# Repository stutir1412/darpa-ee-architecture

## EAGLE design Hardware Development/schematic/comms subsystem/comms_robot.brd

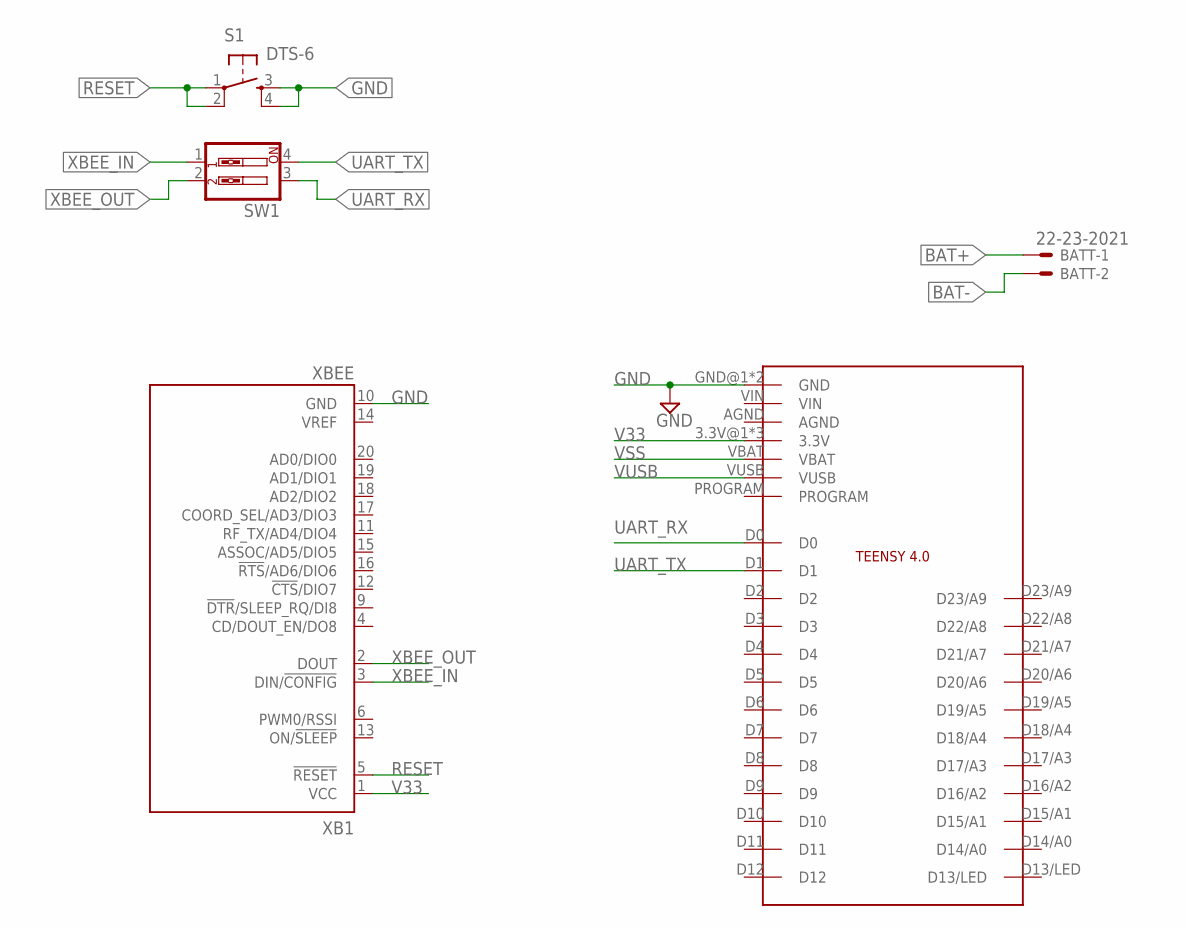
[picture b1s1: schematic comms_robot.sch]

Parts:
BATT: 22-23-2021
S1: DTS-6
SW1: SW_DIP-2; EDG-02
U$1: TEENSY4.0
XB1: XBEE

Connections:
BAT+: BATT.1
BAT-: BATT.2
GND: S1.3, S1.4, U$1.GND@1 (GND), U$1.GND@2 (GND), XB1.10 (GND)
RESET: S1.1, S1.2, XB1.5 (!RESET)
UART_RX: SW1.3, U$1.D0
UART_TX: SW1.4, U$1.D1
V33: U$1.3.3V@1 (3.3V), U$1.3.3V@2 (3.3V), U$1.ON/OFF (3.3V), XB1.1 (VCC)
VSS: U$1.VBAT
VUSB: U$1.VUSB
XBEE_IN: SW1.1, XB1.3 (DIN/!CONFIG)
XBEE_OUT: SW1.2, XB1.2 (DOUT)

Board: 2 copper layers, 5 parts (0 on the bottom side), 7 nets, no tracks yet.

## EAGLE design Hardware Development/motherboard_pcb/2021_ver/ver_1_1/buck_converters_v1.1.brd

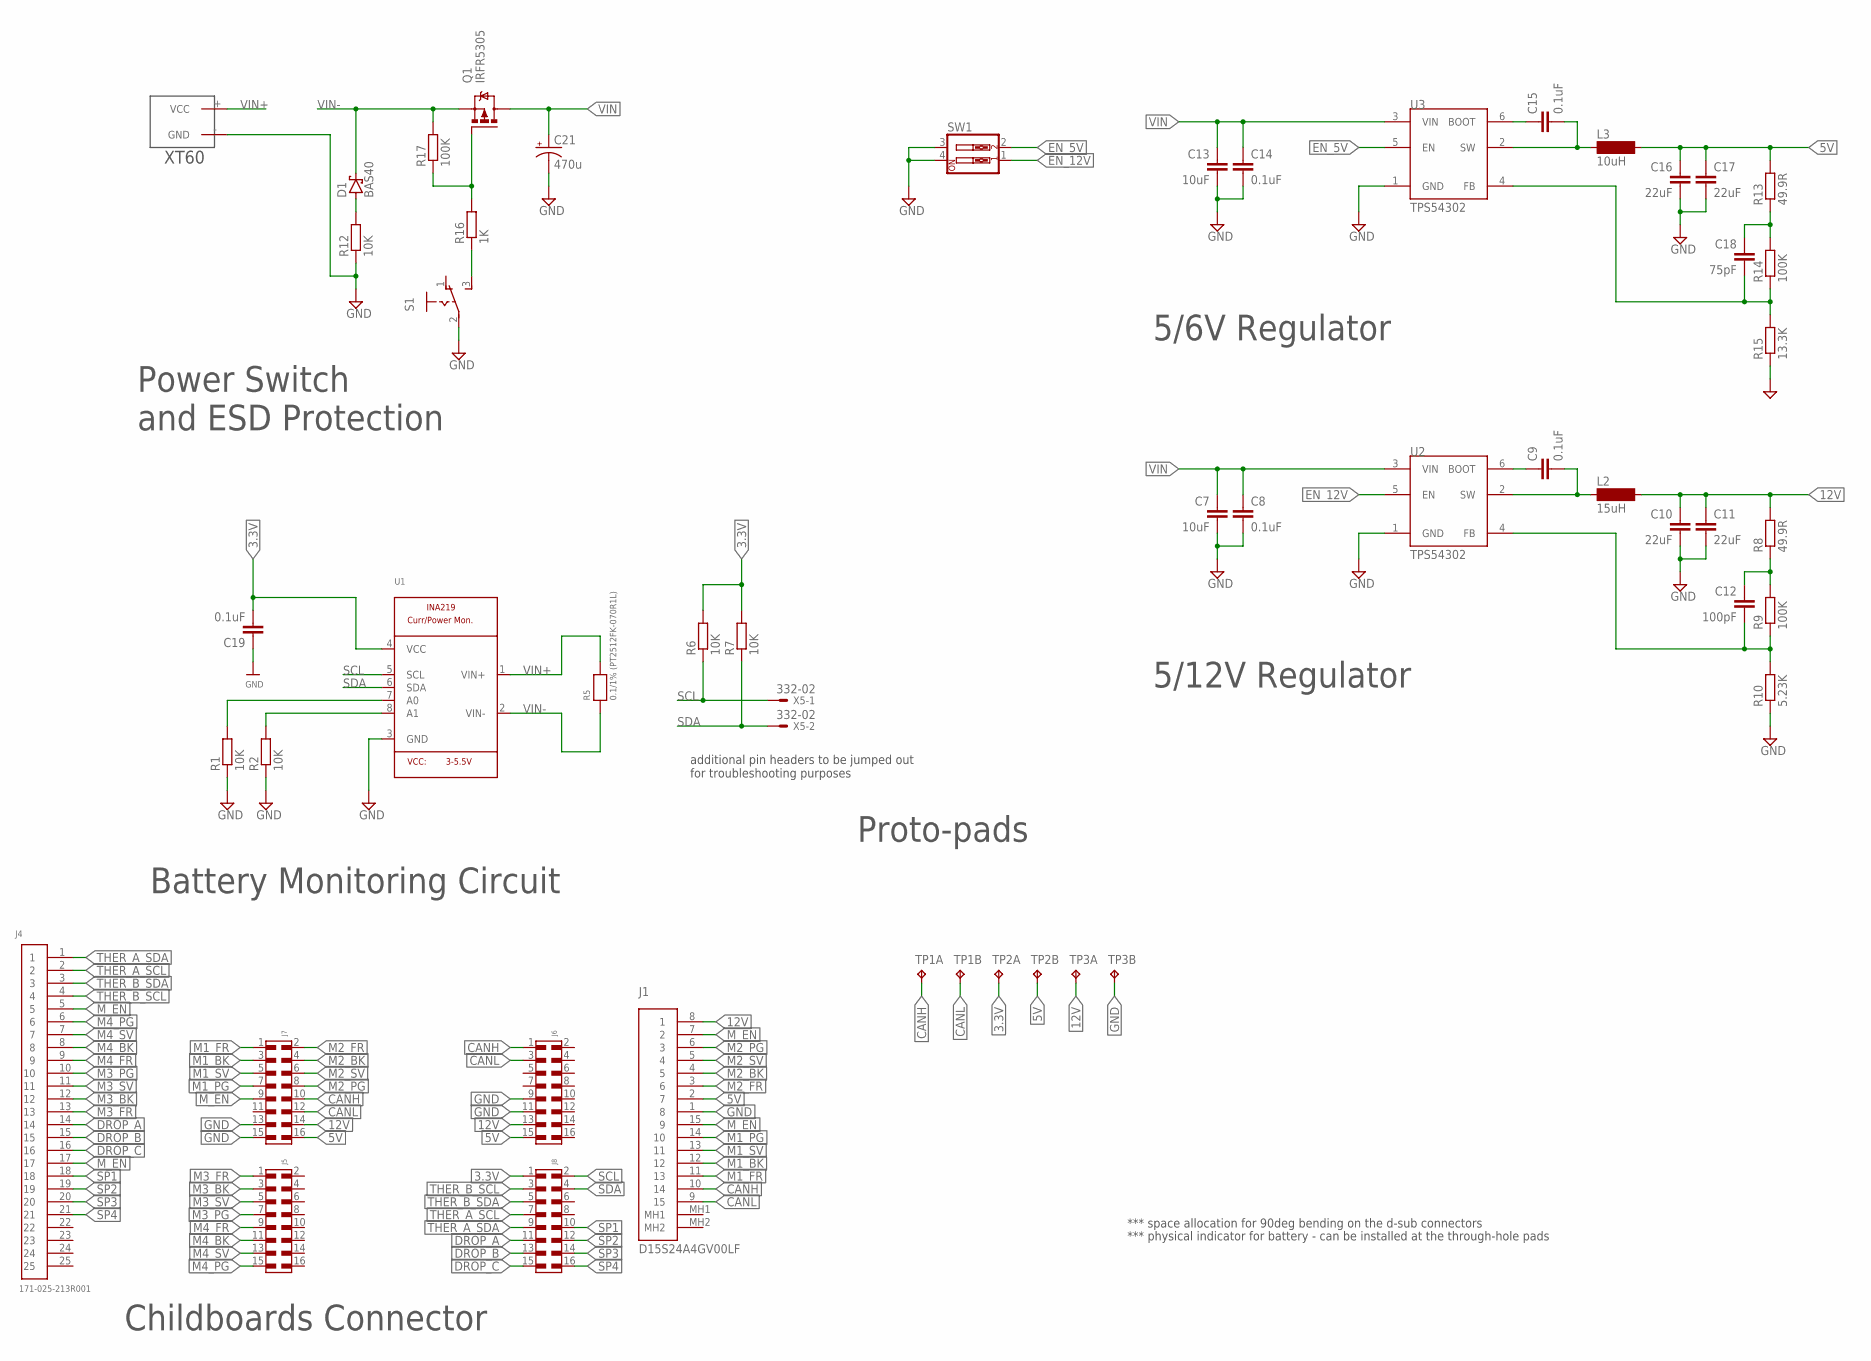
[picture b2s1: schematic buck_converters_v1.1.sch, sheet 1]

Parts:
C7, C13: 10uF; C0805
C8, C9, C14, C15, C19: 0.1uF; C0805
C10, C11, C16, C17: 22uF; C0805
C12: 100pF; C0805
C18: 75pF; C0805
C21: 470u; 153CLV-1010
D1: BAS40; SOT23
J1: D15S24A4GV00LF
J4: 171-025-213R001
J5, J6, J8: 6120XX20621_61201620621; 61201620621
J7: 6123XX20621_61231620621; 61231620621
L2: 15uH; SM-NE29
L3: 10uH; SM-NE29
Q1: IRFR5305; D-PAK_TO252AA
R1, R2, R6, R7, R12: 10K; R0805
R5: 0.1/1% (PT2512FK-070R1L); 2512
R8, R13: 49.9R; R0805
R9, R14, R17: 100K; R0805
R10: 5.23K; R0805
R15: 13.3K; R0805
R16: 1K; R0805
S1: 255SB
SW1: SW_DIP-2; EDG-02
TP1, TP2, TP3: TP2P2-38-17; P2-38-17
U1: INA219; SOT23-8
U2, U3: TPS54302; SOT23-6
U$9: XT60
X5: 332-02

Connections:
3.3V: C19.2, J8.1, R6.2, R7.2, TP2.TP-1, U1.4 (VCC); also elsewhere on the board
5V: C16.1, C17.1, J1.2 (7), J6.15, J7.16, L3.2, R13.2, TP2.TP-2; also elsewhere on the board
12V: C10.1, C11.1, J1.8 (1), J6.13, J7.14, L2.2, R8.2, TP3.TP-1; also elsewhere on the board
CANH: J1.10 (14), J6.1, J7.10, TP1.TP-1; also elsewhere on the board
CANL: J1.9 (15), J6.3, J7.12, TP1.TP-2; also elsewhere on the board
DROP_A: J4.14, J8.11; also elsewhere on the board
DROP_B: J4.15, J8.13; also elsewhere on the board
DROP_C: J4.16, J8.15; also elsewhere on the board
EN_5V: SW1.2, U3.5 (EN)
EN_12V: SW1.1, U2.5 (EN)
GND: C7.2, C8.2, C10.2, C11.2, C13.2, C14.2, C16.2, C17.2, C19.1, C21.-, J1.1 (8), J6.9, J6.11, J7.13, J7.15, R1.1, R2.1, R10.1, R12.1, R15.1, S1.2, SW1.3, SW1.4, TP3.TP-2, U1.3 (GND), U2.1 (GND), U3.1 (GND), U$9.- (GND); also elsewhere on the board
M1_BK: J1.12, J7.3; also elsewhere on the board
M1_FR: J1.11 (13), J7.1; also elsewhere on the board
M1_PG: J1.14 (10), J7.7; also elsewhere on the board
M1_SV: J1.13 (11), J7.5; also elsewhere on the board
M2_BK: J1.4 (5), J7.4; also elsewhere on the board
M2_FR: J1.3 (6), J7.2; also elsewhere on the board
M2_PG: J1.6 (3), J7.8; also elsewhere on the board
M2_SV: J1.5 (4), J7.6; also elsewhere on the board
M3_BK: J4.12, J5.3; also elsewhere on the board
M3_FR: J4.13, J5.1; also elsewhere on the board
M3_PG: J4.10, J5.7; also elsewhere on the board
M3_SV: J4.11, J5.5; also elsewhere on the board
M4_BK: J4.8, J5.11; also elsewhere on the board
M4_FR: J4.9, J5.9; also elsewhere on the board
M4_PG: J4.6, J5.15; also elsewhere on the board
M4_SV: J4.7, J5.13; also elsewhere on the board
M_EN: J1.7 (2), J1.15 (9), J4.5, J4.17, J7.9; also elsewhere on the board
unnamed: R2.2, U1.8 (A1)
unnamed: C12.1, R8.1, R9.2
unnamed: C12.2, R9.1, R10.2, U2.4 (FB)
unnamed: R1.2, U1.7 (A0)
unnamed: C9.1, U2.6 (BOOT)
unnamed: C9.2, L2.1, U2.2 (SW)
unnamed: C18.1, R13.1, R14.2
unnamed: C18.2, R14.1, R15.2, U3.4 (FB)
unnamed: C15.1, U3.6 (BOOT)
unnamed: C15.2, L3.1, U3.2 (SW)
unnamed: D1.1 (A), R12.2
unnamed: R16.1, S1.3 (S)
unnamed: Q1.1 (G), R16.2, R17.1
SCL: J8.2, R6.1, U1.5 (SCL), X5.1; also elsewhere on the board
SDA: J8.4, R7.1, U1.6 (SDA), X5.2; also elsewhere on the board
SP1: J4.18, J8.10; also elsewhere on the board
SP2: J4.19, J8.12; also elsewhere on the board
SP3: J4.20, J8.14; also elsewhere on the board
SP4: J4.21, J8.16; also elsewhere on the board
THER_A_SCL: J4.2, J8.7; also elsewhere on the board
THER_A_SDA: J4.1, J8.9; also elsewhere on the board
THER_B_SCL: J4.4, J8.3; also elsewhere on the board
THER_B_SDA: J4.3, J8.5; also elsewhere on the board
VIN: C7.1, C8.1, C13.1, C14.1, C21.+, Q1.4 (D), U2.3 (VIN), U3.3 (VIN)
VIN+: R5.2, U1.1 (VIN+), U$9.+ (VCC)
VIN-: D1.3 (C), Q1.3 (S), R5.1, R17.2, U1.2 (VIN-)

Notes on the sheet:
Power Switch and ESD Protection
additional pin headers to be jumped out for troubleshooting purposes
Battery Monitoring Circuit
5/6V Regulator
5/12V Regulator
Childboards Connector
Proto-pads
*** space allocation for 90deg bending on the d-sub connectors
*** physical indicator for battery - can be installed at the through-hole pads

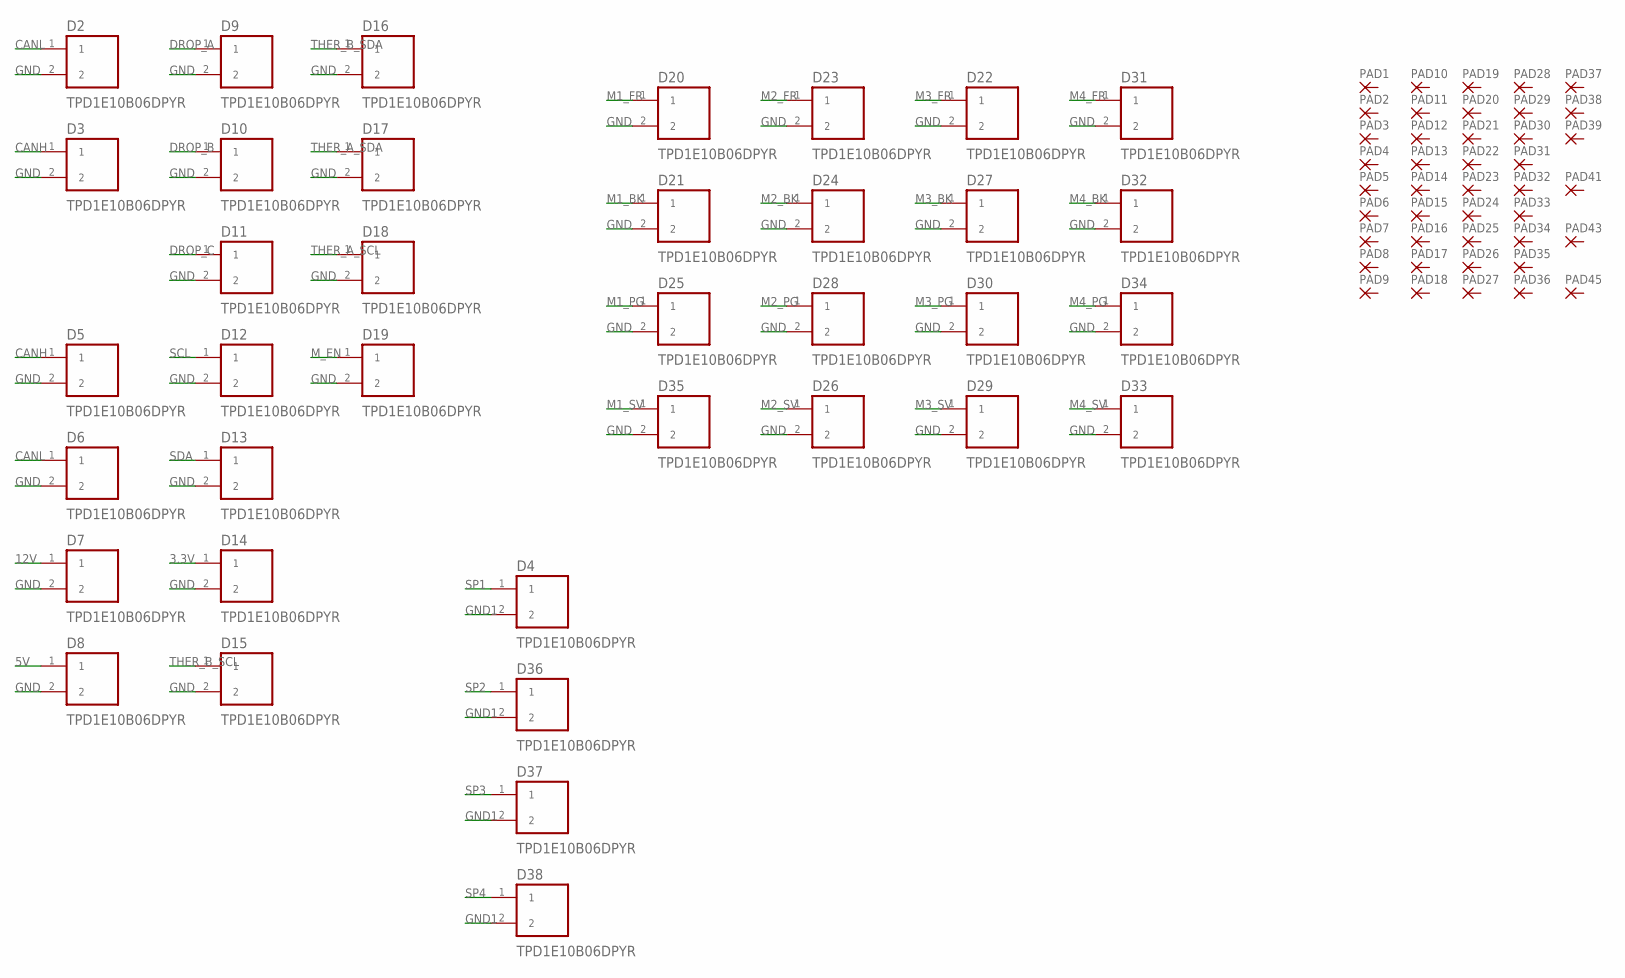
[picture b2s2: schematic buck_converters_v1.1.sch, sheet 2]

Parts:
D2, D3, D4, D5, D6, D7, D8, D9, D10, D11, D12, D13, D14, D15, D16, D17, D18, D19, D20, D21, D22, D23, D24, D25, D26, D27, D28, D29, D30, D31, D32, D33, D34, D35, D36, D37, D38: TPD1E10B06DPYR; DIO_TPD1E05U06DPYR
PAD1, PAD2, PAD3, PAD4, PAD5, PAD6, PAD7, PAD8, PAD9, PAD10, PAD11, PAD12, PAD13, PAD14, PAD15, PAD16, PAD17, PAD18, PAD19, PAD20, PAD21, PAD22, PAD23, PAD24, PAD25, PAD26, PAD27, PAD28, PAD29, PAD30, PAD31, PAD32, PAD33, PAD34, PAD35, PAD36, PAD37, PAD38, PAD39, PAD41, PAD43, PAD45: 2,54/1,1

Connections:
3.3V: D14.1; also elsewhere on the board
5V: D8.1; also elsewhere on the board
12V: D7.1; also elsewhere on the board
CANH: D3.1, D5.1; also elsewhere on the board
CANL: D2.1, D6.1; also elsewhere on the board
DROP_A: D9.1; also elsewhere on the board
DROP_B: D10.1; also elsewhere on the board
DROP_C: D11.1; also elsewhere on the board
GND: D2.2, D3.2, D5.2, D6.2, D7.2, D8.2, D9.2, D10.2, D11.2, D12.2, D13.2, D14.2, D15.2, D16.2, D17.2, D18.2, D19.2, D20.2, D21.2, D22.2, D23.2, D24.2, D25.2, D26.2, D27.2, D28.2, D29.2, D30.2, D31.2, D32.2, D33.2, D34.2, D35.2; also elsewhere on the board
GND1: D4.2, D36.2, D37.2, D38.2
M1_BK: D21.1; also elsewhere on the board
M1_FR: D20.1; also elsewhere on the board
M1_PG: D25.1; also elsewhere on the board
M1_SV: D35.1; also elsewhere on the board
M2_BK: D24.1; also elsewhere on the board
M2_FR: D23.1; also elsewhere on the board
M2_PG: D28.1; also elsewhere on the board
M2_SV: D26.1; also elsewhere on the board
M3_BK: D27.1; also elsewhere on the board
M3_FR: D22.1; also elsewhere on the board
M3_PG: D30.1; also elsewhere on the board
M3_SV: D29.1; also elsewhere on the board
M4_BK: D32.1; also elsewhere on the board
M4_FR: D31.1; also elsewhere on the board
M4_PG: D34.1; also elsewhere on the board
M4_SV: D33.1; also elsewhere on the board
M_EN: D19.1; also elsewhere on the board
SCL: D12.1; also elsewhere on the board
SDA: D13.1; also elsewhere on the board
SP1: D4.1; also elsewhere on the board
SP2: D36.1; also elsewhere on the board
SP3: D37.1; also elsewhere on the board
SP4: D38.1; also elsewhere on the board
THER_A_SCL: D18.1; also elsewhere on the board
THER_A_SDA: D17.1; also elsewhere on the board
THER_B_SCL: D15.1; also elsewhere on the board
THER_B_SDA: D16.1; also elsewhere on the board

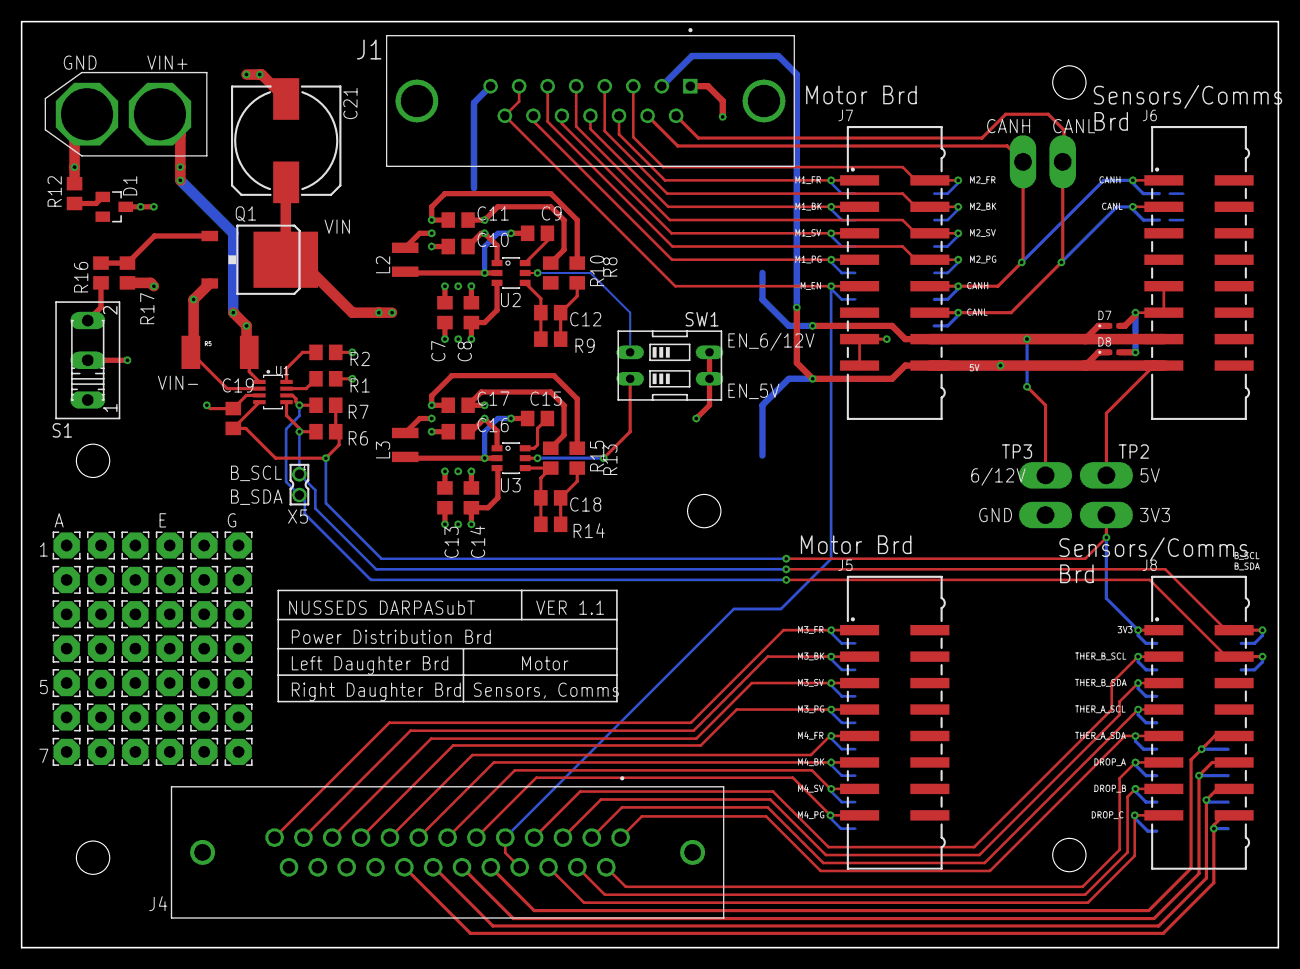
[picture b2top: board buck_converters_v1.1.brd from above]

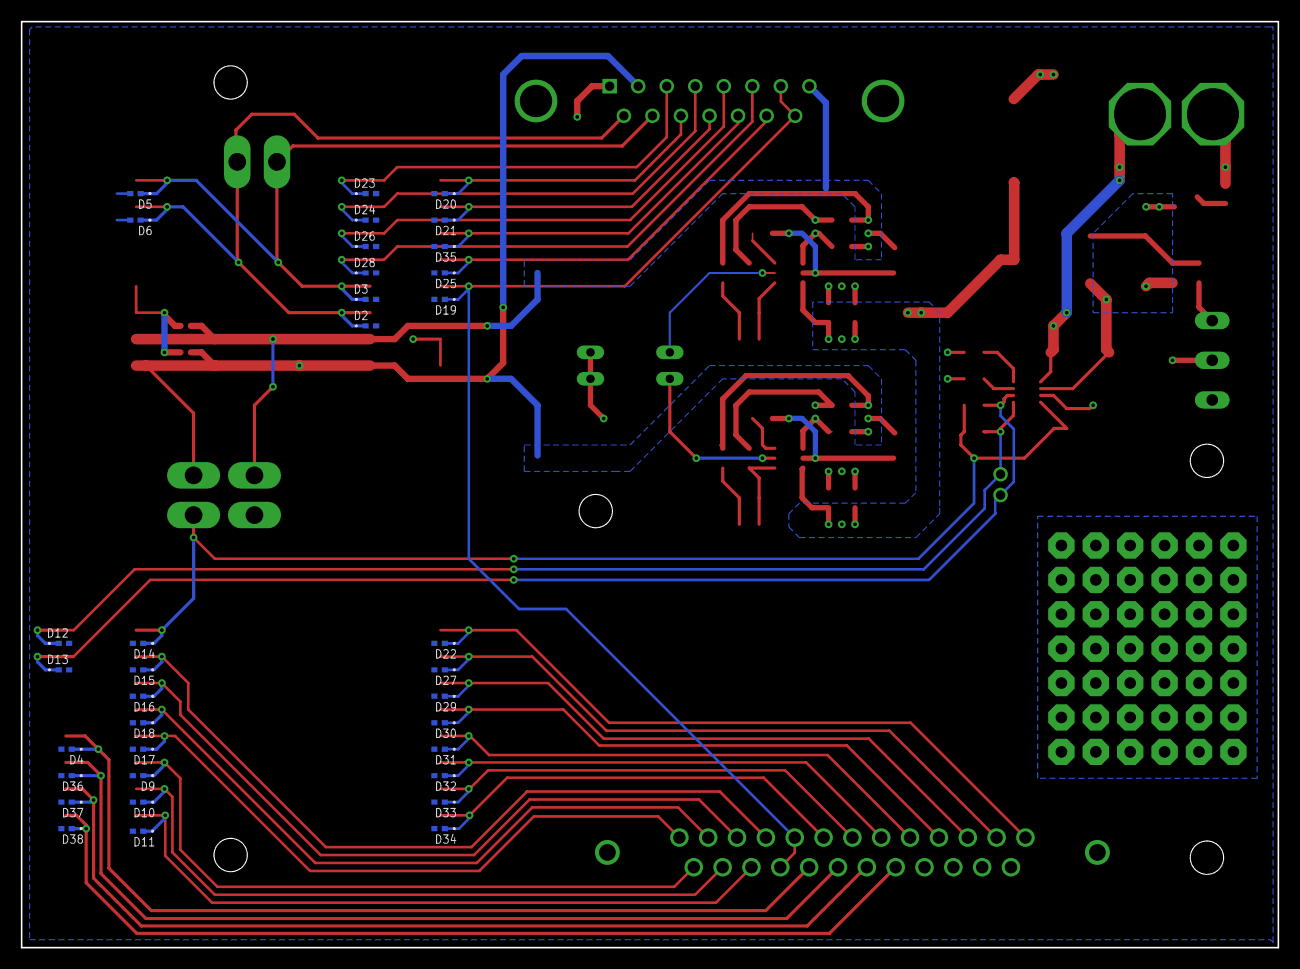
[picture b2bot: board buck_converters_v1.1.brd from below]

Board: 2 copper layers, 120.7 x 88.9 mm, 127 parts (35 on the bottom side), 55 nets.

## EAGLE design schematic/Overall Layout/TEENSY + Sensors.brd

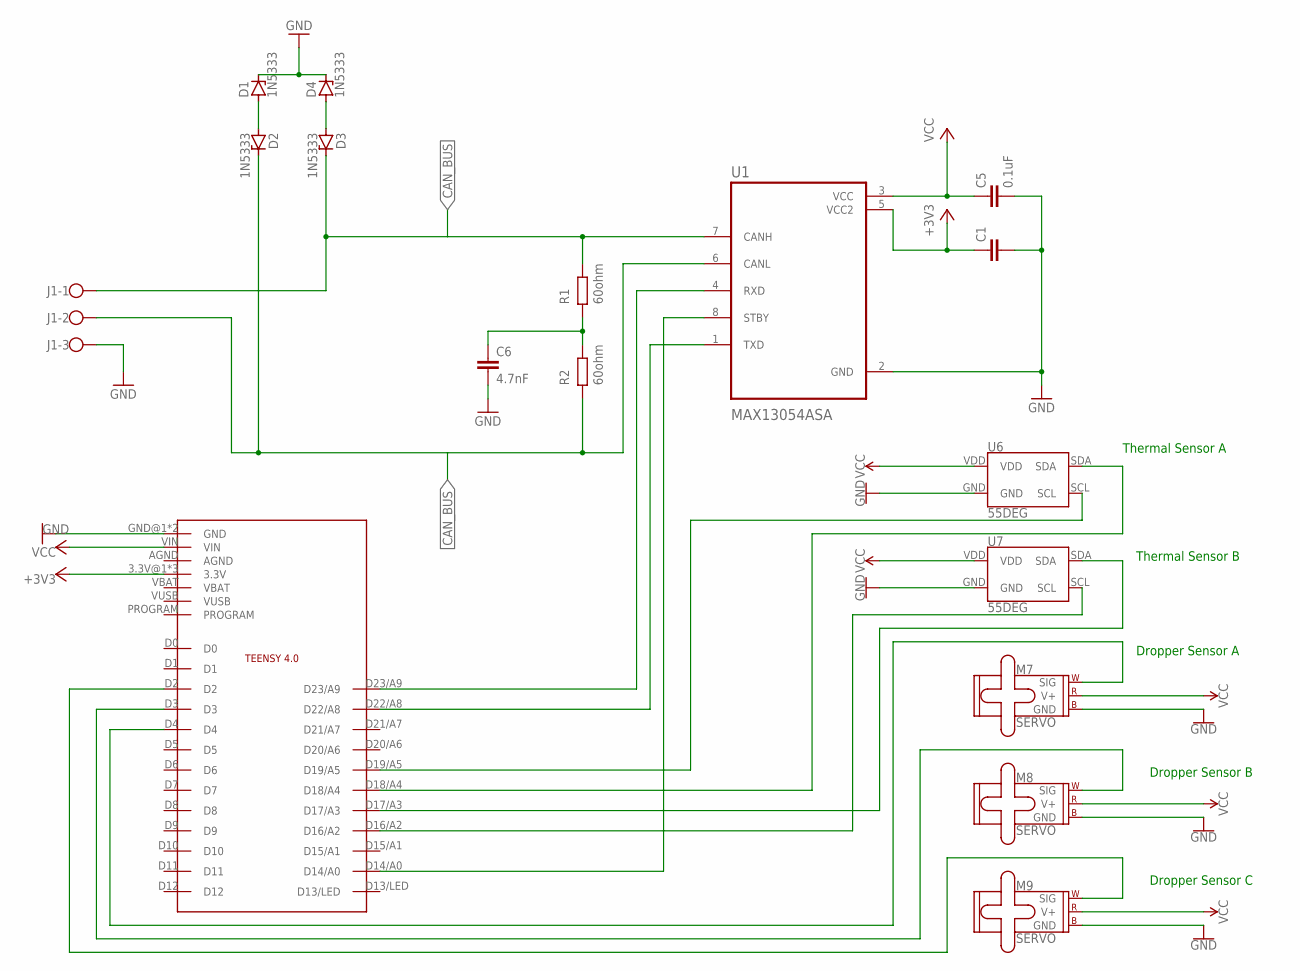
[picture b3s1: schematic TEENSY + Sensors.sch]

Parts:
C1: C2,5-3; C2.5-3
C5: 0.1uF; C2.5-3
C6: 4.7nF; C2.5-3
D1, D2, D3, D4: 1N5333; C1702-15
J1: W237-103
M7, M8, M9: SERVO; 1X03
U1: MAX13054ASA; SOIC127P600X175-8N
U6, U7: 55DEG; MLX90540_MLX90640
U$2: TEENSY4.0

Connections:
+3V3: C1.1, U1.5 (VCC2), U$2.3.3V@1 (3.3V), U$2.3.3V@2 (3.3V), U$2.ON/OFF (3.3V)
CAN_BUS: D3.C, J1.1, U1.7 (CANH)
GND: C1.2, C5.2, C6.2, D1.C, D4.C, J1.3, M7.3 (GND), M8.3 (GND), M9.3 (GND), U1.2 (GND), U6.GND, U7.GND, U$2.GND@1 (GND), U$2.GND@2 (GND)
unnamed: U1.4 (RXD), U$2.D23/A9
unnamed: U1.1 (TXD), U$2.D22/A8
unnamed: D1.A, D2.A
unnamed: D2.C, J1.2, U1.6 (CANL)
unnamed: D3.A, D4.A
unnamed: U1.8 (STBY), U$2.D14/A0
unnamed: U7.SDA, U$2.D17/A3
unnamed: U7.SCL, U$2.D16/A2
unnamed: M7.1 (SIG), U$2.D4
unnamed: M8.1 (SIG), U$2.D3
unnamed: M9.1 (SIG), U$2.D2
unnamed: U6.SCL, U$2.D19/A5
unnamed: U6.SDA, U$2.D18/A4
VCC: C5.1, M7.2 (V+), M8.2 (V+), M9.2 (V+), U1.3 (VCC), U6.VDD, U7.VDD, U$2.VIN

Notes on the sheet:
Dropper Sensor A
Dropper Sensor B
Dropper Sensor C
Thermal Sensor A
Thermal Sensor B

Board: 2 copper layers, 15 parts (0 on the bottom side), 17 nets, no tracks yet.

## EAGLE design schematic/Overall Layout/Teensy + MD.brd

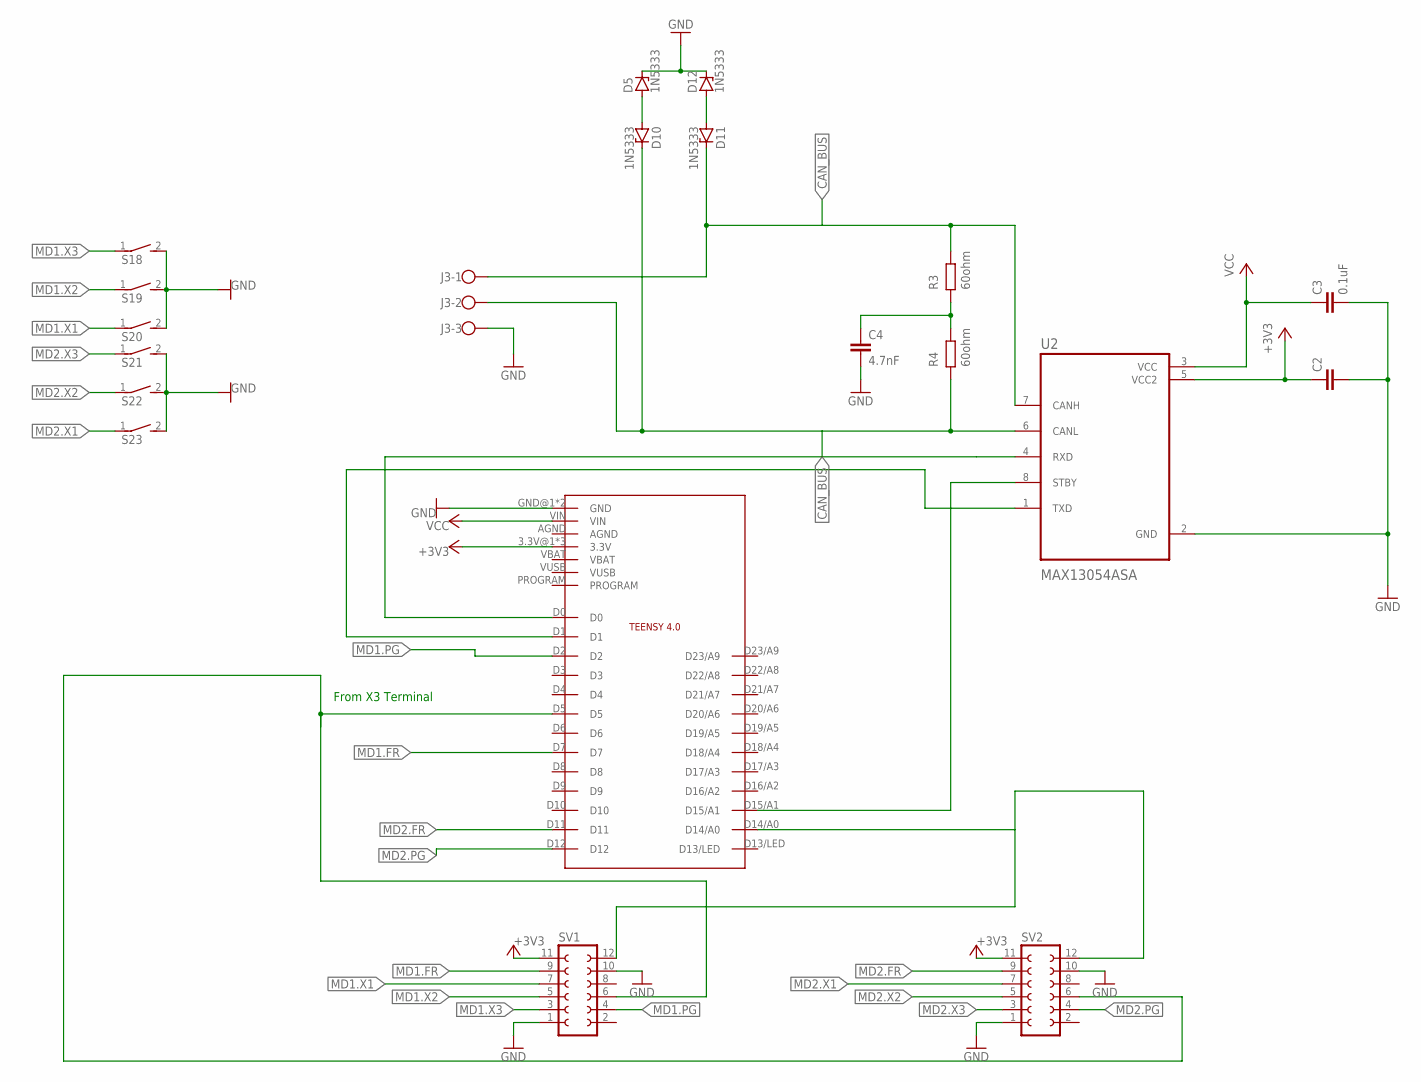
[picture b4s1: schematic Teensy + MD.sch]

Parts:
C2: C2,5-3; C2.5-3
C3: 0.1uF; C2.5-3
C4: 4.7nF; C2.5-3
D5, D10, D11, D12: 1N5333; C1702-15
J3: W237-103
S18, S19, S20, S21, S22, S23: DS01E; DS-01
SV1, SV2: FE06-2
U2: MAX13054ASA; SOIC127P600X175-8N
U$3: TEENSY4.0

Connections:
+3V3: C2.1, SV1.11, SV2.11, U2.5 (VCC2), U$3.3.3V@1 (3.3V), U$3.3.3V@2 (3.3V), U$3.ON/OFF (3.3V)
CAN_BUS: D11.C, J3.1, U2.7 (CANH)
GND: C2.2, C3.2, C4.2, D5.C, D12.C, J3.3, S18.2, S19.2, S20.2, S21.2, S22.2, S23.2, SV1.1, SV1.10, SV2.1, SV2.10, U2.2 (GND), U$3.GND@1 (GND), U$3.GND@2 (GND)
MD1.5V: SV1.6, SV2.6, U$3.D5
MD1.FR: SV1.9, U$3.D7
MD1.PG: SV1.4, U$3.D2
MD1.X1: S20.1, SV1.7
MD1.X2: S19.1, SV1.5
MD1.X3: S18.1, SV1.3
MD2.BK: SV1.12, SV2.12, U$3.D14/A0
MD2.FR: SV2.9, U$3.D11
MD2.PG: SV2.4, U$3.D12
MD2.X1: S23.1, SV2.7
MD2.X2: S22.1, SV2.5
MD2.X3: S21.1, SV2.3
unnamed: D10.C, J3.2, U2.6 (CANL)
unnamed: U2.8 (STBY), U$3.D15/A1
unnamed: U2.4 (RXD), U$3.D0
unnamed: U2.1 (TXD), U$3.D1
unnamed: D5.A, D10.A
unnamed: D11.A, D12.A
VCC: C3.1, U2.3 (VCC), U$3.VIN

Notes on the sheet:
From X3 Terminal

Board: 2 copper layers, 18 parts (0 on the bottom side), 22 nets, no tracks yet.

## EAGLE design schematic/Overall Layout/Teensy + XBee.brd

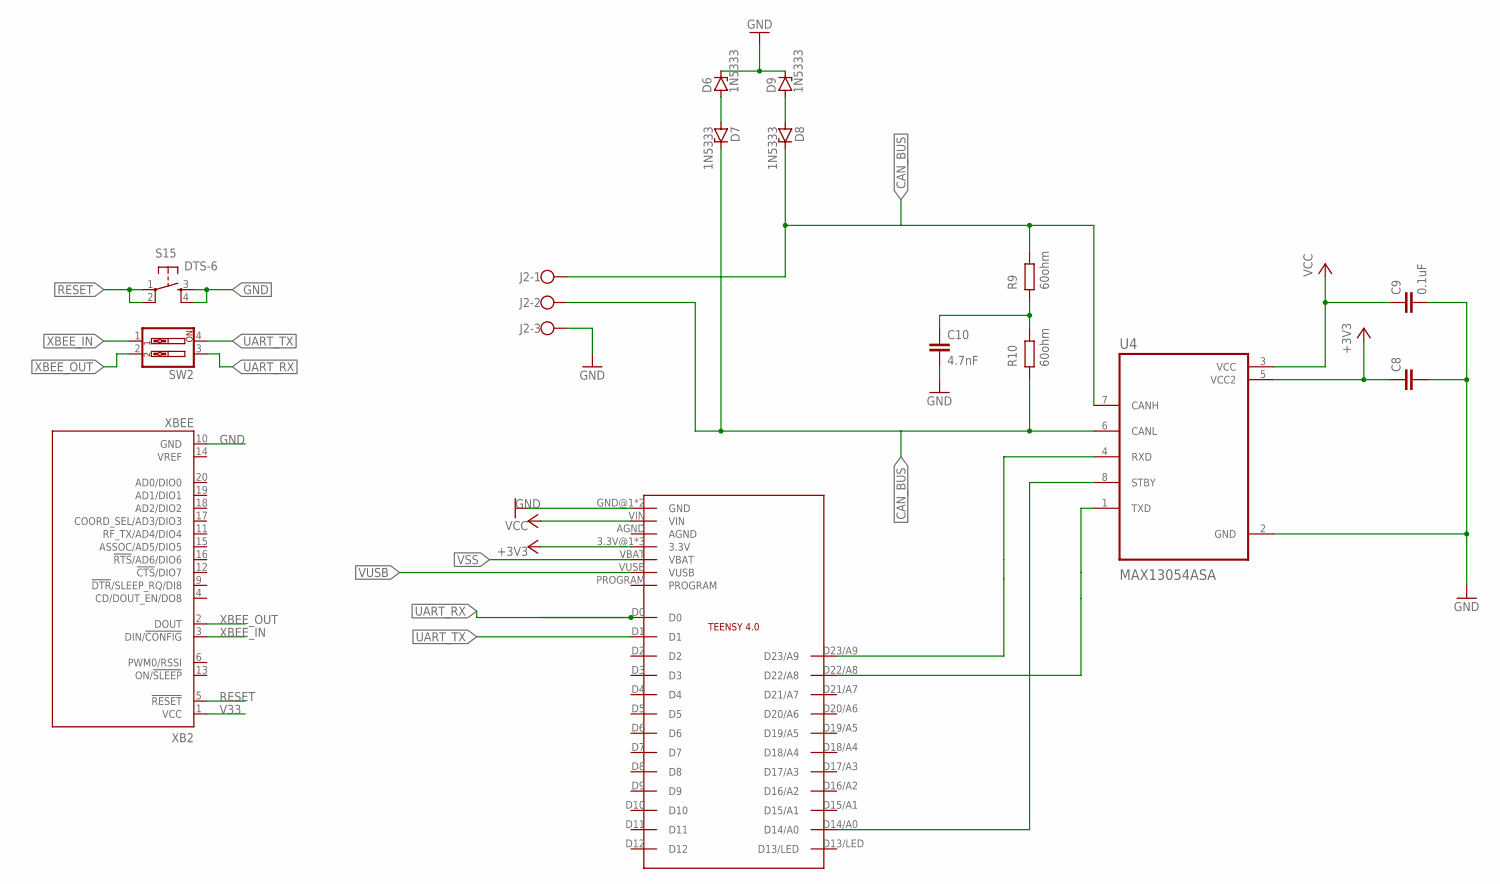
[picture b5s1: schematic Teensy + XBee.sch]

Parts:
C8: C2,5-3; C2.5-3
C9: 0.1uF; C2.5-3
C10: 4.7nF; C2.5-3
D6, D7, D8, D9: 1N5333; C1702-15
J2: W237-103
S15: DTS-6
SW2: SW_DIP-2; EDG-02
U4: MAX13054ASA; SOIC127P600X175-8N
U$6: TEENSY4.0
XB2: XBEE

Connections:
+3V3: C8.1, U4.5 (VCC2), U$6.3.3V@1 (3.3V), U$6.3.3V@2 (3.3V), U$6.ON/OFF (3.3V)
CAN_BUS: D8.C, J2.1, U4.7 (CANH)
GND: C8.2, C9.2, C10.2, D6.C, D9.C, J2.3, S15.3, S15.4, U4.2 (GND), U$6.GND@1 (GND), U$6.GND@2 (GND), XB2.10 (GND)
unnamed: D7.C, J2.2, U4.6 (CANL)
unnamed: U4.8 (STBY), U$6.D14/A0
unnamed: U4.4 (RXD), U$6.D23/A9
unnamed: U4.1 (TXD), U$6.D22/A8
unnamed: D6.A, D7.A
unnamed: D8.A, D9.A
RESET: S15.1, S15.2, XB2.5 (!RESET)
UART_RX: SW2.3, U$6.D0
UART_TX: SW2.4, U$6.D1
V33: XB2.1 (VCC)
VCC: C9.1, U4.3 (VCC), U$6.VIN
VSS: U$6.VBAT
VUSB: U$6.VUSB
XBEE_IN: SW2.1, XB2.3 (DIN/!CONFIG)
XBEE_OUT: SW2.2, XB2.2 (DOUT)

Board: 2 copper layers, 13 parts (0 on the bottom side), 15 nets, no tracks yet.

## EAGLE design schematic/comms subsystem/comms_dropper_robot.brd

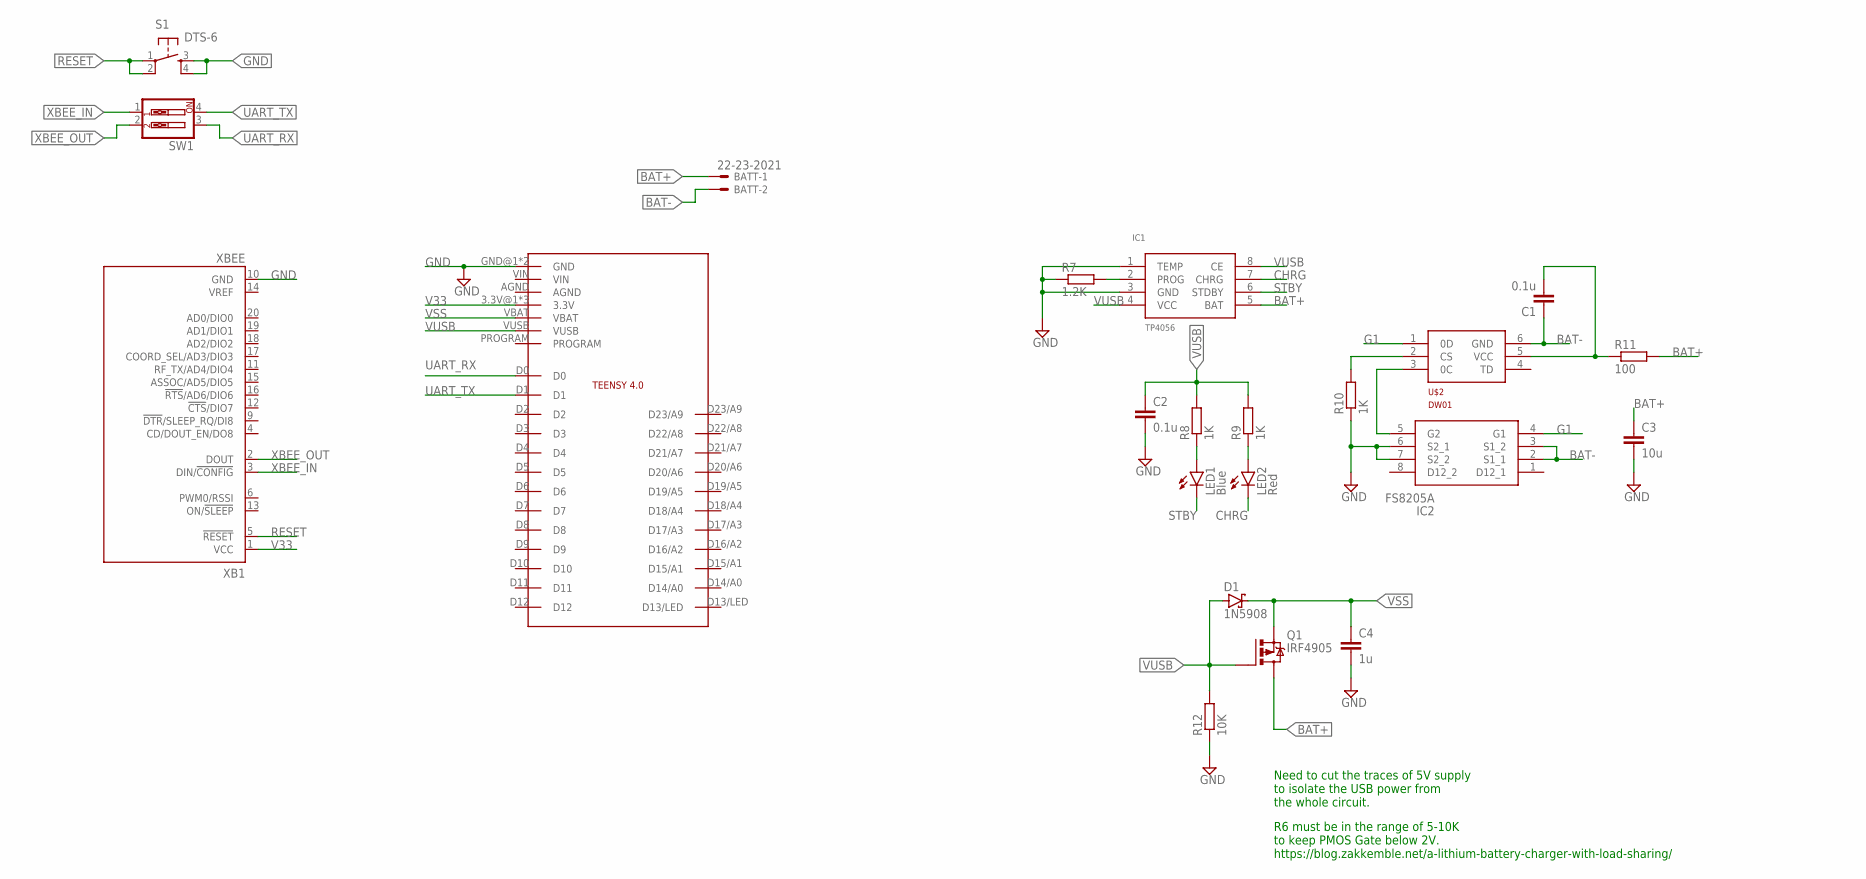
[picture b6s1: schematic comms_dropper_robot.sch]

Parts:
BATT: 22-23-2021
C1, C2: 0.1u; C2.5-3
C3: 10u; C2.5-3
C4: 1u; C2.5-3
D1: 1N5908; C4111-15
IC1: TP4056; SOP-8
IC2: FS8205A; SOP65P640X120-8N
LED1: Blue; LED3MM
LED2: Red; LED3MM
Q1: IRF4905; TO220BH
R7: 1.2K; R0805
R8, R9, R10: 1K; R0805
R11: 100; R0805
R12: 10K; R0805
S1: DTS-6
SW1: SW_DIP-2; EDG-02
U$1: TEENSY4.0
U$2: DW01; SOT23-6
XB1: XBEE

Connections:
BAT+: BATT.1, C3.1, IC1.5 (BAT), Q1.D, R11.2
BAT-: BATT.2, C1.1, IC2.2 (S1_1), IC2.3 (S1_2), U$2.6 (GND)
CHRG: IC1.7 (CHRG), LED2.K (C)
G1: IC2.4 (G1), U$2.1 (0D)
GND: C2.2, C3.2, C4.2, IC1.1 (TEMP), IC1.3 (GND), IC2.6 (S2_1), IC2.7 (S2_2), R7.1, R10.1, R12.1, S1.3, S1.4, U$1.GND@1 (GND), U$1.GND@2 (GND), XB1.10 (GND)
unnamed: IC2.5 (G2), U$2.3 (0C)
unnamed: IC1.2 (PROG), R7.2
unnamed: R10.2, U$2.2 (CS)
unnamed: C1.2, R11.1, U$2.5 (VCC)
unnamed: LED1.A, R8.1
unnamed: LED2.A, R9.1
RESET: S1.1, S1.2, XB1.5 (!RESET)
STBY: IC1.6 (STDBY), LED1.K (C)
UART_RX: SW1.3, U$1.D0
UART_TX: SW1.4, U$1.D1
V33: U$1.3.3V@1 (3.3V), U$1.3.3V@2 (3.3V), U$1.ON/OFF (3.3V), XB1.1 (VCC)
VSS: C4.1, D1.C, Q1.S, U$1.VBAT
VUSB: C2.1, D1.A, IC1.4 (VCC), IC1.8 (CE), Q1.G, R8.2, R9.2, R12.2, U$1.VUSB
XBEE_IN: SW1.1, XB1.3 (DIN/!CONFIG)
XBEE_OUT: SW1.2, XB1.2 (DOUT)

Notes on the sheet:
Need to cut the traces of 5V supply to isolate the USB power from the whole circuit.
R6 must be in the range of 5-10K to keep PMOS Gate below 2V. https://blog.zakkemble.net/a-lithium-battery-charger-with-load-sharing/

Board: 2 copper layers, 22 parts (0 on the bottom side), 20 nets, no tracks yet.

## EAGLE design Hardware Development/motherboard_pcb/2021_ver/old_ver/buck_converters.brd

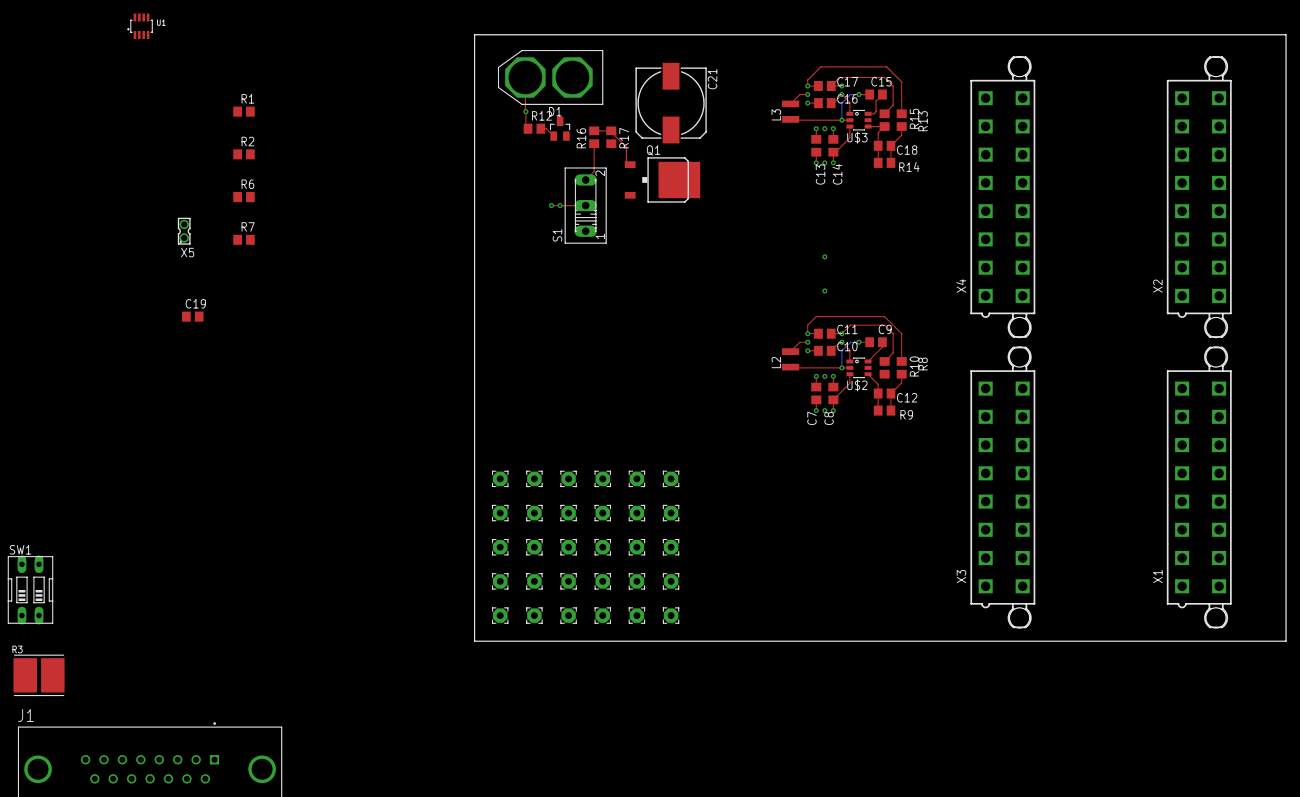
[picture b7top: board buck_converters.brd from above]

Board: 2 copper layers, 120.7 x 90.2 mm, 74 parts (0 on the bottom side), 22 nets.

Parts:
C7, C13: 10uF; C0805
C8, C9, C14, C15, C19: 0.1uF; C0805
C10, C11, C16, C17: 22uF; C0805
C12: 100pF; C0805
C18: 75pF; C0805
C21: 153CLV-1010
D1: BAS40; SOT23
J1: D15S24A4GV00LF
L2: 15uH; SM-NE29
L3: 10uH; SM-NE29
PAD1, PAD2, PAD3, PAD4, PAD5, PAD6, PAD7, PAD8, PAD9, PAD10, PAD11, PAD12, PAD13, PAD14, PAD15, PAD16, PAD17, PAD18, PAD19, PAD20, PAD21, PAD22, PAD23, PAD24, PAD25, PAD26, PAD27, PAD28, PAD29, PAD30: 2,15/1,0
Q1: IRFR5305; D-PAK_TO252AA
R1, R2, R6, R7, R12, R16, R17: 10K; R0805
R3: VISHAY_WSHP2818R0100FEAVISHAY_WSHP2818R0100FEA_0_0; VISHAY_WSHP2818R0100FEA_0
R8, R13: 49.9R; R0805
R9, R14: 100K; R0805
R10: 5.23K; R0805
R15: 13.3K; R0805
S1: 255SB
SW1: EDG-02
U1: SOT23-8
U$2, U$3: TPS54302; SOT23-6
U$9: XT60
X1, X2, X3, X4: 5566-16
X5: 332-02

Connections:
3.3V: C19.2, R6.2, R7.2, U1.4
5V: C16.1, C17.1, L3.2, R13.2
12V: C10.1, C11.1, L2.2, R8.2
GND: C7.2, C8.2, C10.2, C11.2, C13.2, C14.2, C16.2, C17.2, C19.1, C21.-, R1.1, R2.1, R10.1, R12.1, R15.1, S1.2, SW1.3, SW1.4, U1.3, U$2.1, U$3.1, U$9.-
unnamed: R2.2, U1.8
unnamed: C12.1, R8.1, R9.2
unnamed: C12.2, R9.1, R10.2, U$2.4
unnamed: R1.2, U1.7
unnamed: C9.1, U$2.6
unnamed: C9.2, L2.1, U$2.2
unnamed: C18.1, R13.1, R14.2
unnamed: C18.2, R14.1, R15.2, U$3.4
unnamed: C15.1, U$3.6
unnamed: C15.2, L3.1, U$3.2
unnamed: D1.1, R12.2
unnamed: R16.1, S1.3
unnamed: Q1.1, R16.2, R17.1
SCL: R6.1, U1.5, X5.1
SDA: R7.1, U1.6, X5.2
VIN: C7.1, C8.1, C13.1, C14.1, C21.+, Q1.4, U$2.3, U$3.3
VIN+: R3.2, U1.1, U$9.+
VIN-: D1.3, Q1.3, R3.1, R17.2, U1.2

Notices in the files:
parts and their libraries:
smt_male_header_16ways: Copyright: Würth Elektronik
SparkFun-IC-Special-Function: Licensing: Creative Commons ShareAlike 4.0 International - https://creativecommons.org/licenses/by-sa/4.0
